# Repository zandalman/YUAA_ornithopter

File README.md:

# YUAA Ornithopter Project

An ornithopter is a flying machine that generates thrust and lift by imitating the flight of birds. Ornithopters have the advantages of maneuverability, versatility, and stealth over traditional aircraft, making them useful in aerial reconnaissance, search & rescue, and agricultural surveying. In this project, we design and build an ornithopter capable of sustained flight and maneuvering.

# Software

## Controls

Our ornithopter is highly customizable, with many adjustable variables to cater to various flying styles. Such include:

 - **maxFrequency**: Maximum flapping frequency reached when throttle is pulled all the way up. The higher the value, the faster the wings flap, and the more sensitive the flapping frequency will be.
 - **zeroThrottleAngle**: Our ornithopter glides when the throttle is set to 0, or a range close to 0 denoted by **deadZone**. This variable adjusts the angle (in degrees) above the horizontal the wing rests at in glide mode.
 - **levelAngle**: Angle above the horizontal at center of flapping cycle.
 - **maxAmplitude**: How far above and below **levelAngle** the wing flaps.
 - **maxRollPhaseShift**: Roll is achieved by adding a phase delay to the wing opposite to the side of which you want to turn. This variable defines the maximum phase shift when the magnitude of the roll control is at its maximum.
 - **maxPitchAngle**: Pitch is elevated by raising the **levelAngle** and lowered by decreasing it. This variable denotes the maximum change to **levelAngle** when pitch is set to its maximum magnitude. The higher this is, the more sensitive the pitch control.
 - **maxYawAngle**: Yaw is achieved by lowering the **levelAngle** on the side you yaw towards and raising it on the opposite side. This variable defines the maximum deviation to **levelAngle** when yaw is set to its maximum magnitude. The higher this is, the more sensitive the yaw control.
 - **deadZone**: For every control, there is a range in which the value is interpreted as 0. This allows for gliding and makes it easy to keep a purely level angle. The higher this value is, the larger that dead zone.
 - **delayTime**: Frequency at which a new control is registered and a new servo output is generated. The lower this is, the smoother the controls.

All other parameters should be left unmodified.

## Behind the Scenes

The remote controller has 8 channels, each mapped to a control (roll, pitch, yaw, etc.). For each of the controls, we normalize the digital input to a value between 0 and 1 or -1 and 1. There are three control modes—normal, amp, and basic—that reconfigure the layout of the controls. Every iteration of the event loop, we input the controls into a function called **updatePosition()**, which renders new servo positions corresponding to the positions in the flap cycle. **updatePosition()** is a void function, meaning it directly updates the global variables instead of returning an output. The function relies on a unit circle methodology, where the wing position is the *sin* of a rotating point around a circle, and the linear velocity of the rotating point is determined by the throttle. The other controls module the angle and phase.

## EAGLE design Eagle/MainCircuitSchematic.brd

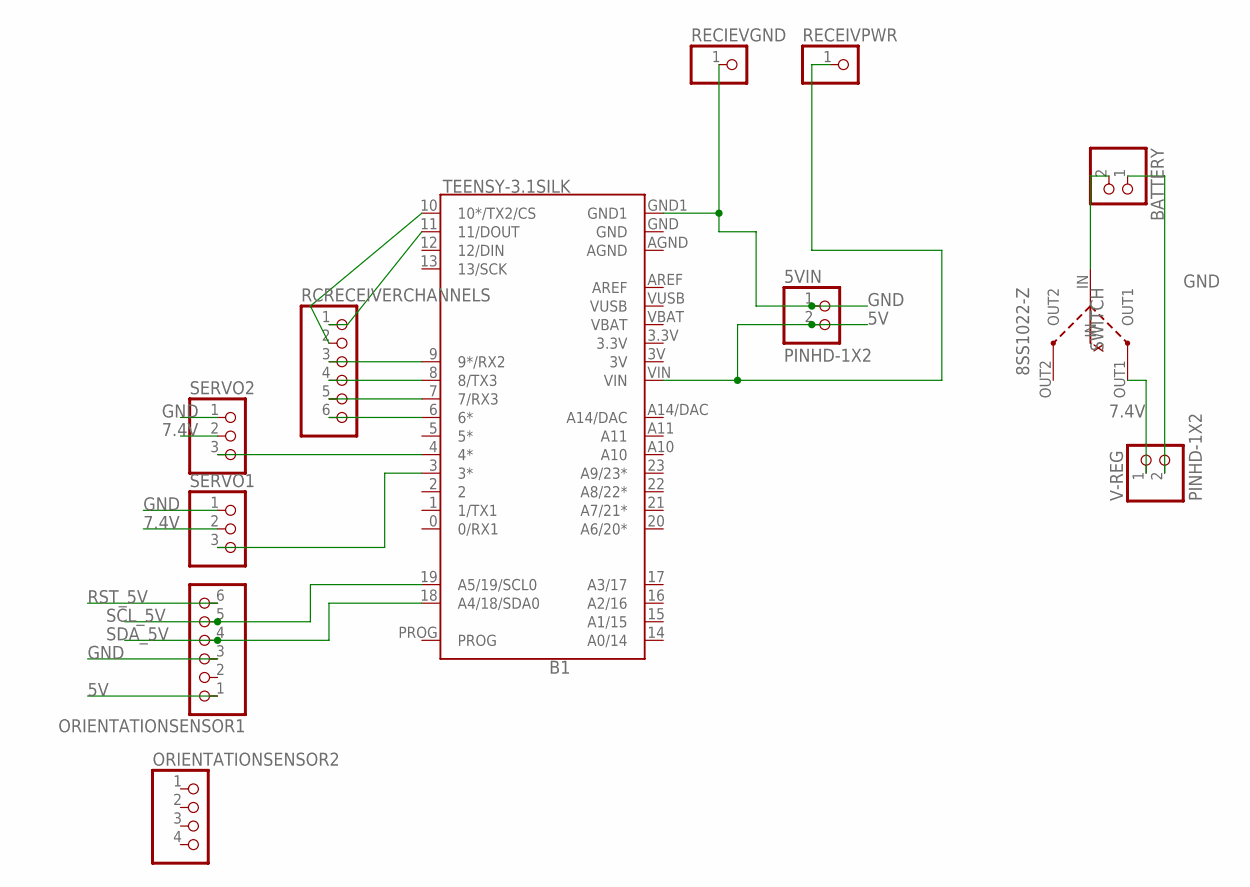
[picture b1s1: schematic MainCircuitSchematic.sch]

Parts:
5VIN: PINHD-1X2; 1X02
B1: TEENSY-3.1SILK; TEENSY-3.1
BATTERY: PINHD-1X2; 1X02
ORIENTATIONSENSOR1: HEADER-1X676MIL; 1X06_ROUND_76
ORIENTATIONSENSOR2: HEADER-1X476MIL; 1X04_ROUND_76
RCRECEIVERCHANNELS: PINHD-1X6; 1X06
RECEIVPWR: PINHD-1X1; 1X01
RECIEVGND: PINHD-1X1; 1X01
SERVO1, SERVO2: PINHD-1X3CB; 1X03-CLEANBIG
SWITCH: 8SS1022-Z
V-REG: PINHD-1X2; 1X02

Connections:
3.3V: B1.3.3V
3V: B1.3V
5V: 5VIN.2, B1.VIN, ORIENTATIONSENSOR1.1, RECEIVPWR.1
7.4V: SERVO1.2, SERVO2.2, SWITCH.OUT1, V-REG.1
AGND: B1.AGND
GND: 5VIN.1, B1.GND, B1.GND1, BATTERY.1, ORIENTATIONSENSOR1.3, RECIEVGND.1, SERVO1.1, SERVO2.1, V-REG.2
unnamed: B1.11 (11/DOUT), RCRECEIVERCHANNELS.1
unnamed: B1.10 (10*/TX2/CS), RCRECEIVERCHANNELS.2
unnamed: B1.9 (9*/RX2), RCRECEIVERCHANNELS.3
unnamed: B1.8 (8/TX3), RCRECEIVERCHANNELS.4
unnamed: B1.7 (7/RX3), RCRECEIVERCHANNELS.5
unnamed: B1.6 (6*), RCRECEIVERCHANNELS.6
unnamed: B1.4 (4*), SERVO2.3
unnamed: B1.3 (3*), SERVO1.3
unnamed: BATTERY.2, SWITCH.IN
RST_5V: ORIENTATIONSENSOR1.6
SCL_5V: B1.19 (A5/19/SCL0), ORIENTATIONSENSOR1.5
SDA_5V: B1.18 (A4/18/SDA0), ORIENTATIONSENSOR1.4
VBAT: B1.VBAT
VUSB: B1.VUSB

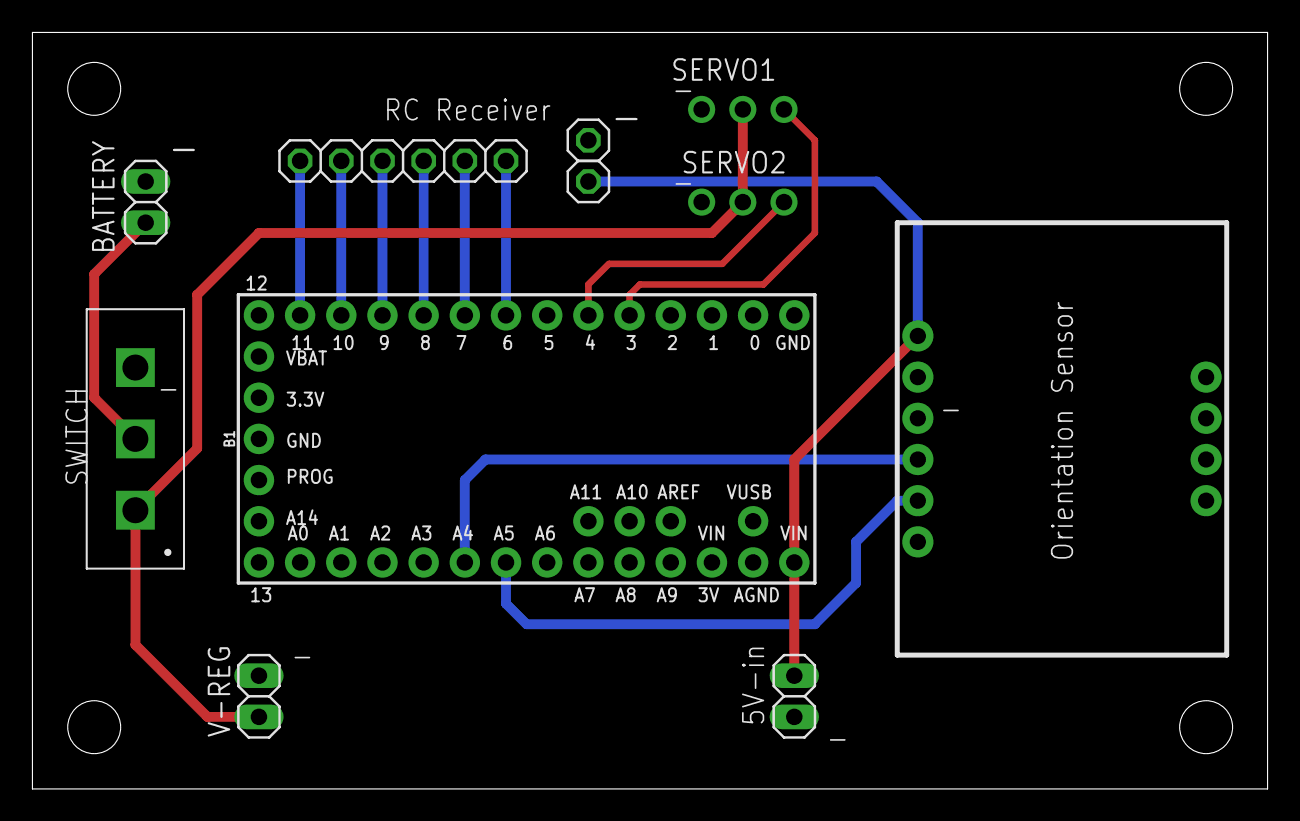
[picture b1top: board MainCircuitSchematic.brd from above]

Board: 2 copper layers, 76.2 x 46.7 mm, 12 parts (0 on the bottom side), 14 nets.

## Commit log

2020-10-11 Added files.
2020-10-30 Framework for gyro/wings/RC
2020-10-30 Fixed links problem (maybe)
2020-11-01 detailed description of what I did
2020-11-01 Removed whatever
2020-11-15 added motor control sketch
2021-01-10 Add files via upload
    1-10-2021 version, labeled and servo pins swapped with rc receiver
2021-01-10 Add files via upload
    1-10-2021 schematic file
2021-01-24 Add files via upload
    fixed receiver and servo pins
2021-01-31 changed around files
2021-01-31 Added a few files
2021-01-31 last updated 1/25/21
2021-02-14 added switch to design, removed excess receiver pins
2021-02-14 all testing files
2021-02-21 added throttle; test file for thursday
2021-02-26 comments, fixing organization, gyro updates
2021-03-10 random change to show Kai
2021-03-10 Undo
2021-03-10 For Kai
2021-03-10 Added new file
2021-03-13 changed to FS-A8S receiver
2021-03-14 Update Kai.ino
    Added nextPos function
2021-03-14 Update Kai.ino
    More changes
2021-03-21 assigned channels, cleaned up RC code
2021-03-24 added test file with two wings
2021-03-27 Create controls.ino
    Latest version of controls.
2021-03-28 Update controls.ino
    Fixed directional controls
2021-04-04 preliminary ornithopter sensor falling functions
2021-04-06 RC acts as on/off toggle for wings
2021-04-11 Update controls.ino
    Now with servos! :D
2021-04-11 Update controls.ino
    I think you will enjoy this.
2021-04-11 I think you will enjoy this :D
2021-04-15 Added RC control for testing
2021-04-23 Add files via upload
    orientation tracking code
2021-04-25 Update controls.ino
    Comments for variables
2021-04-25 Update controls.ino
    Amplitude controls, toggler
2021-04-25 Update README.md
    Practice editing readme
2021-04-25 Update README.md
    Code
2021-04-27 small changes
2021-05-01 Added control modes
2021-05-02 Update README.md
    Description for Controls
2021-05-02 Update controls.ino
    const
2021-05-25 Cleaned up files
2021-05-25 Cleaning up files some more
2021-05-25 Added new files

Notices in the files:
parts and their libraries:
SparkFun-Boards: Licensing: Creative Commons ShareAlike 4.0 International - https://creativecommons.org/licenses/by-sa/4.0
microbuilder: This work is placed in the public domain, and may be freely used for commercial and non-commercial work with the following conditions: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
